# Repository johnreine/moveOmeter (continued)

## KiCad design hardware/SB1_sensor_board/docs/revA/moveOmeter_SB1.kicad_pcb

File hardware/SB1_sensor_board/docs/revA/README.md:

# moveOmeter sensor board SB1 (rev A draft, placed, not routed)

One HLK-LD6004 (60 GHz) and one HLK-LD2450 (24 GHz) on a 70 x 56.5 mm board with TB1's mounting holes. Each sensor
has its own USB-C port and USB-serial chip, so a PC can run both sensors with no mainboard. A 20-pin ribbon carries
5 V in and both serial ports out to the mainboard. Generated 2026-10-25 from `tools/` (same generator as TB1); on
2026-10-26 the ribbon header was stood on end and cut from 26 to 20 pins, and the board re-placed.

**Product arrangement:** two identical SB1s per frame or nightlight, fronts 90 degrees apart in a V with the point toward
the room (`docs/SB1_arrangement.png`).
- **Coverage:** each board points 45 degrees off straight-out, so every direction in front of the wall is within 45
  degrees of one radar's axis. With +/-60 degree radars that leaves 15 degrees to spare at the edges, about 210 degrees
  per radar type, and about 30 degrees of overlap straight ahead. A third board isn't needed.
- **Mainboard:** directly behind the two SB1s. It takes both ribbons on two 2x10 headers that also stand on end, at the
  same height as J3. Each flat cable then runs level, edge-on, and only bends sideways (the easy way) through the 45
  degrees between the boards.

## Open it

Open `moveOmeter_SB1.kicad_pro` in KiCad 10. The schematics are KiCad 8 format until KiCad saves them. Project
libraries: `lib/SB1.kicad_sym` and `lib/SB1.pretty` (radar modules and the front-mount hole, copied from TB1). Run ERC,
then Update PCB from Schematic (F8): it should only refresh fields. Run DRC before routing.

## Sheets

| Sheet | File | Contents |
| --- | --- | --- |
| Power_USB | power_usb.kicad_sch | 2x USB-C + USBLC6 + CH340C, 2x TPS2113A 5 V mux, BAT54C + LP5907 3.3 V logic rail, 20-pin ribbon, INA219 address jumper |
| LD6004 | ld6004.kicad_sch | TLV62569 3.3 V buck, INA219, rail discharge, TX gate, ESD, board-mounted module |
| LD2450 | ld2450.kicad_sch | TPS2051C 5 V switch, INA219, rail discharge, TX gate, ESD, board-mounted module |

## How it works

- **Power:** each sensor's 5 V comes from a TPS2113A that prefers the ribbon's 5 V and falls back to that sensor's
  USB-C. Neither input can back-feed the other (the mux FETs have no body diodes). USB-C A powers the LD6004 and USB-C
  B the LD2450, so each sensor gets a whole USB port. The 3.3 V logic rail (CH340Cs, monitors, gates) comes from
  either sensor's 5 V through a BAT54C and an LP5907 LDO.
- **Serial:** the sensor's TX goes to both its CH340C and the ribbon through 1k each. A 3-input AND gate
  (SN74LVC1G11) drives the sensor's RX from the CH340C TX, the ribbon TX and a "sensor rail is up" sense, so either
  host can talk (an idle UART line is high). The gate's output is held low while the sensor is off, so nothing
  back-powers it.
- **On/off:** each sensor is on by default (100k pull-up on EN).
  - The mainboard turns it off by pulling its ribbon EN line low.
  - The PC turns it off by asserting DTR with RTS released (a 2N7002 from RTS# to DTR#). Opening the port asserts both
    lines, which leaves the sensor on. In pyserial: `ser.rts = False; ser.dtr = True` for off, `ser.dtr = False` for
    on.
  - When EN goes low, the rail-discharge FET pulls the sensor rail to 0 V, so a power cycle is a clean reset.
- **Status lines:** LD6004 P20 and the LD2450 switch fault flag go to the ribbon and to each CH340C's CTS# input.
- **Current monitors:** INA219s at 0x40 (LD6004) and 0x44 (LD2450). Bridge solder jumper ADDR B on the second board
  of a pair to move them to 0x41 / 0x45. The I2C pull-ups are on the mainboard.

## Ribbon (J3, 2x10 shrouded header, 2.54 mm)

Wire n on the flat cable is pin n, and the cable is straight through, so the mainboard's headers use the same
pinout. The two +5 V wires and every serial and I2C wire have a ground wire on each side. The four enable / status
lines barely change, so they're grouped at the end without grounds between them.

| Pin | Signal | Pin | Signal |
| --- | --- | --- | --- |
| 1 | GND | 2 | +5 V in |
| 3 | +5 V in | 4 | GND |
| 5 | LD6004 TX (mainboard to sensor) | 6 | GND |
| 7 | LD6004 RX (sensor to mainboard) | 8 | GND |
| 9 | LD2450 TX (mainboard to sensor) | 10 | GND |
| 11 | LD2450 RX (sensor to mainboard) | 12 | GND |
| 13 | I2C SDA | 14 | GND |
| 15 | I2C SCL | 16 | GND |
| 17 | LD6004 enable (low = off) | 18 | LD2450 enable (low = off) |
| 19 | LD6004 P20 | 20 | LD2450 fault (low = fault) |

Seen from behind, pin 1 is at the top, odd pins in the left column, and the shroud's key slot on the left.

UART logic is 3.3 V. Baud rates: LD6004 115200, LD2450 256000. The CH340C makes 256000 as 12 MHz / 47 = 255.3 kbaud
(-0.3 %).

## Layout (70 x 56.5 mm, placed 2026-10-26, not routed)

- **Holes:** TB1's four M3 holes and footprint, with 0.27 in front-mount clearance. J3's shroud sets the board height:
  56.5 mm, 1.5 mm taller than the 70 x 55 mm v0.1 board whose holes it shares (64 mm with the 2x13 header).
- **Front:** LD6004 on the top edge, LD2450 under it (same positions as TB1), and the radar circuitry below them.
- **Back:** the ribbon header J3, a straight shrouded 2x10 standing on end (long side top to bottom), centred
  left-right. Its pins run from just below the LD2450 (27.6 mm from the top edge, pin 1 at the top) to 50.5 mm, and the
  shroud ends about 1 mm from the bottom edge. The cable leaves straight back, edge-on, toward the mainboard.
  - It can't sit behind the radars: no through-hole pins there, so the ground stays solid.
  - It can't sit near a side edge: on one board of each pair that edge is the point of the V, and the plug would hit
    the other board.
  - Also on the back: both USB-C ports on the bottom edge at the corners (bench use; unused in the unit), the
    USB-serial chips, the 5 V muxes and the 3.3 V LDO.
- Nothing is on the side edges: with two identical boards in a V, one board's outer edge is the other's inner edge.
- **Stackup:** 4 layers, F.Cu signals + GND / In1 GND / In2 +3V3 / B.Cu signals + GND. Fill zones after routing.
- **Checks:** all rule checks pass (mount clearance, radar fields of view, no through-hole pins behind the radars,
  edges, nets).

## Ordering

`bom_board.csv` has DigiKey numbers and qty-1 prices: about $49 a board, not counting the two radar modules. The
exception is the CH340C: WCH chips aren't sold by DigiKey or Mouser, so it comes from LCSC (part C84681). Buy a few
spares.

The ribbon cable isn't in the BOM, because its length depends on the mainboard. Any keyed 20-way 2.54 mm IDC cable
with a socket on each end fits. One example is Assmann H3AAH-2006G (LCSC C1770517), which can go in the same order as
the CH340Cs.

## Ready for rev B: mic socket

Rev B (decided on the 10/26 evening drive, not built yet) gets two Adafruit I2S mic breakouts per board. Their socket
is already in the libraries: symbol `SB1:I2S_Mic_Breakout`, footprint `SB1:Adafruit_I2S_Mic_Breakout_Socket_1x06`.

- **Breakouts:** Adafruit 6049 (TDK ICS-43434) or 3421 (Knowles SPH0645). Adafruit's board files show the same
  16.51 x 12.7 mm outline, header, sound-hole position and holes, so either plugs in. Adafruit's 6049 page says the
  ICS-43434 is discontinued and names the SPH0645 as its replacement.
- **Amazon clone (B0FMDGRM8F, silk "MRS179A"), 10/26:** a copy of Adafruit's 6049 layout. From the listing photo: same
  pin order (3V, GND, BCLK, DOUT, LRCL, SEL), same parts, sound hole about 5.3-5.5 mm from the pin row and centred,
  holes about 11.4 mm apart. The board may be up to ~1 mm narrower on the header side, which stays inside the
  footprint's outline. The listing calls SEL an I2S / PDM select; on the ICS-43434 it's the left / right channel
  select, as on Adafruit's board (the chip is I2S only). Fits the same socket.
- **Pins (from Adafruit's board files):** 1 3V, 2 GND, 3 BCLK, 4 DOUT, 5 LRCL (WS), 6 SEL. SEL low = left channel,
  high = right, so the two mics on a board share one data line.
- **Mounting:** a 1x6 female socket (Sullins PPTC061LFBN-RC, 8.5 mm) on SB1's front. Solder the breakout's header
  with its plastic on the chip side (the side shown in Adafruit's photo), so the pins point away from that side and
  the sound hole faces the room. The breakout lies parallel to SB1, its sound hole about 12.6 mm off the board.
  Seen from the front, pin 1 (3V) is at the right, on the square pad.
- **Check print:** `docs/SB1_mic_socket_1to1.pdf` (print at 100 %, check the 50 mm bar). Lay a breakout on it sound
  hole up: the pins should land on the pads with 3V on the square pad, and the sound hole on the cross.
- **Source:** `tools/layout/mkmicfp.py` writes the footprint; `tools/layout/render_micfp.py` draws the check print.

## Regenerating

- `python3 tools/build.py <out>` writes the schematics, symbol library, netlist report and BOM. Parts and nets are in
  `tools/design.py`, ordering data in `tools/vendor.py`.
- `tools/layout/` writes and checks the board (see its README): `plan_sb1.py`, `place_sb1.py`, `mkpcb_sb1.py`,
  `verify_sb1.py`. `render2.py` draws it (`docs/SB1_board.png`). `arrangement.py` draws the three-board sketch.
- Once you edit in KiCad, KiCad is the source of truth.

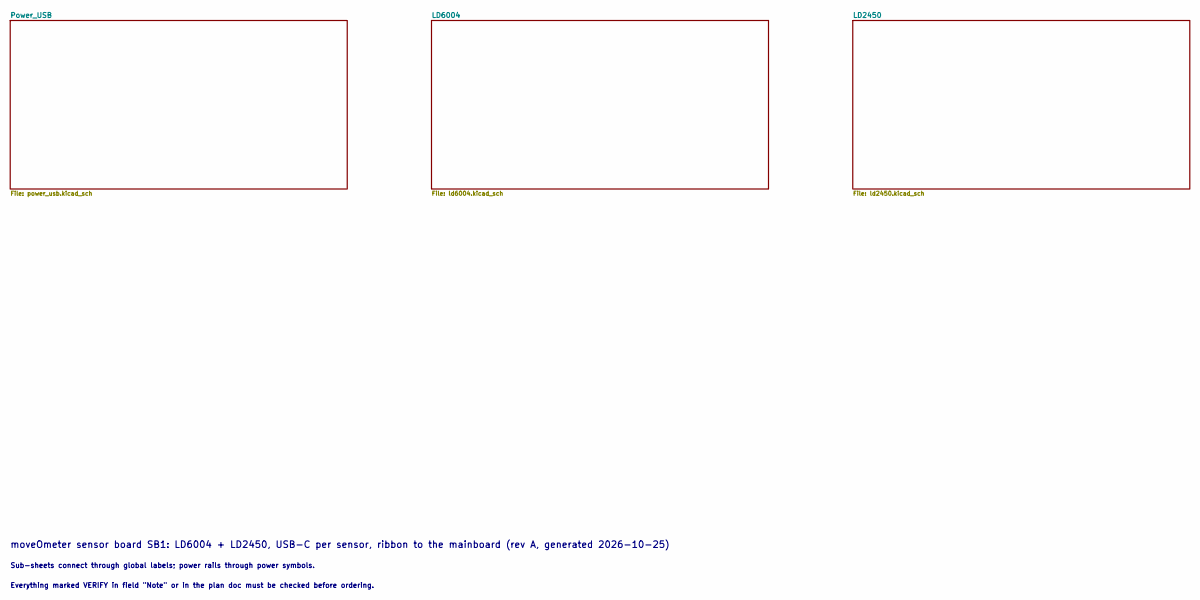
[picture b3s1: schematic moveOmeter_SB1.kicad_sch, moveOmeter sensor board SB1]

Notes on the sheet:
moveOmeter sensor board SB1: LD6004 + LD2450, USB-C per sensor, ribbon to the mainboard (rev A, generated 2026-10-25)
Sub-sheets connect through global labels; power rails through power symbols.
Everything marked VERIFY in field "Note" or in the plan doc must be checked before ordering.

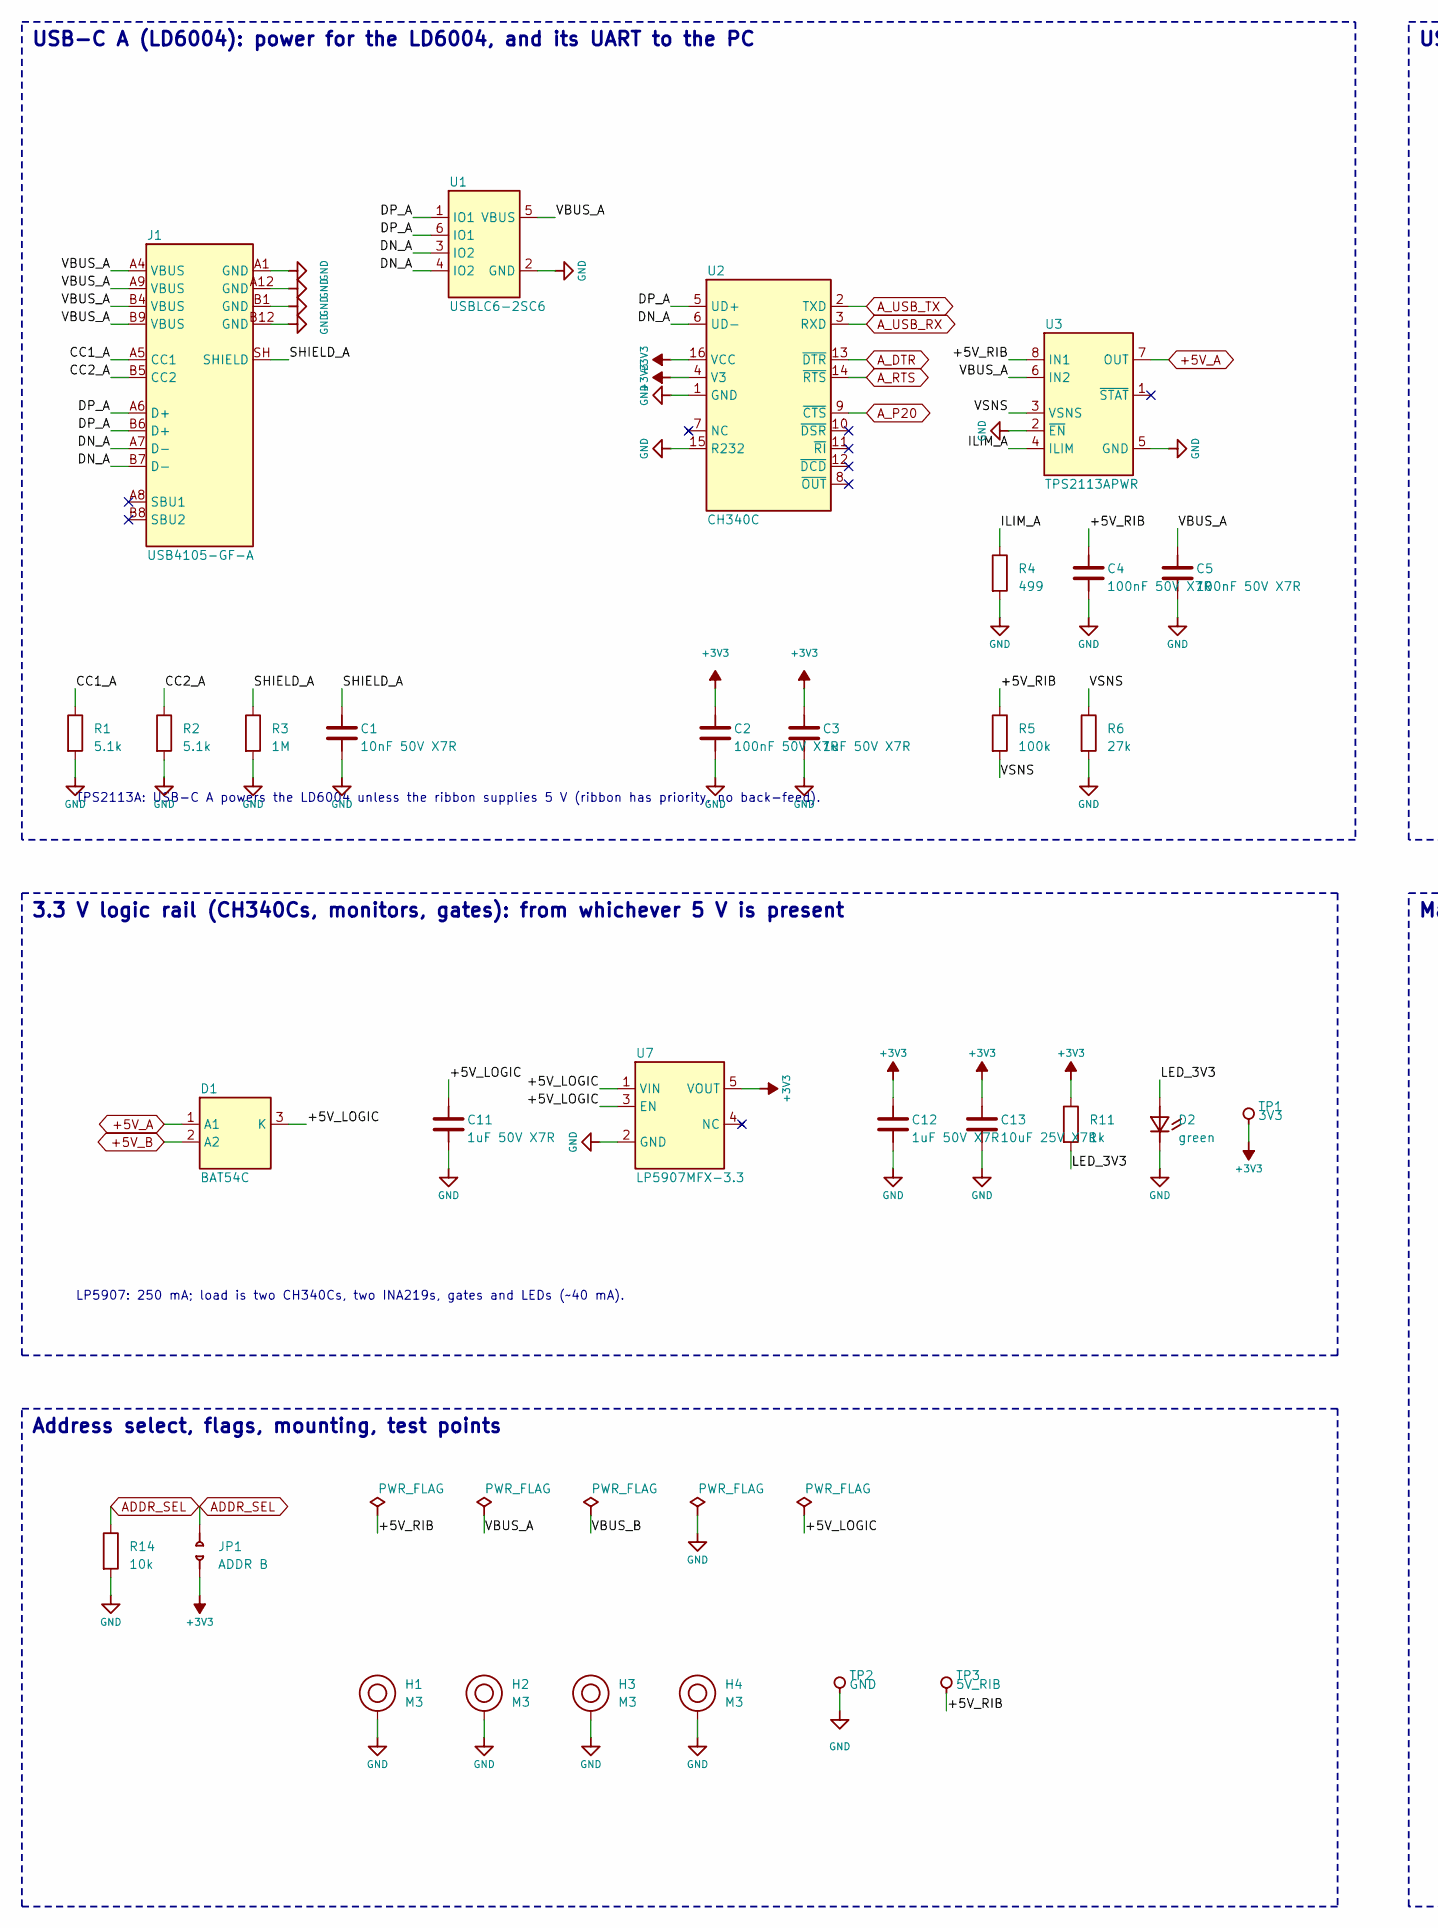
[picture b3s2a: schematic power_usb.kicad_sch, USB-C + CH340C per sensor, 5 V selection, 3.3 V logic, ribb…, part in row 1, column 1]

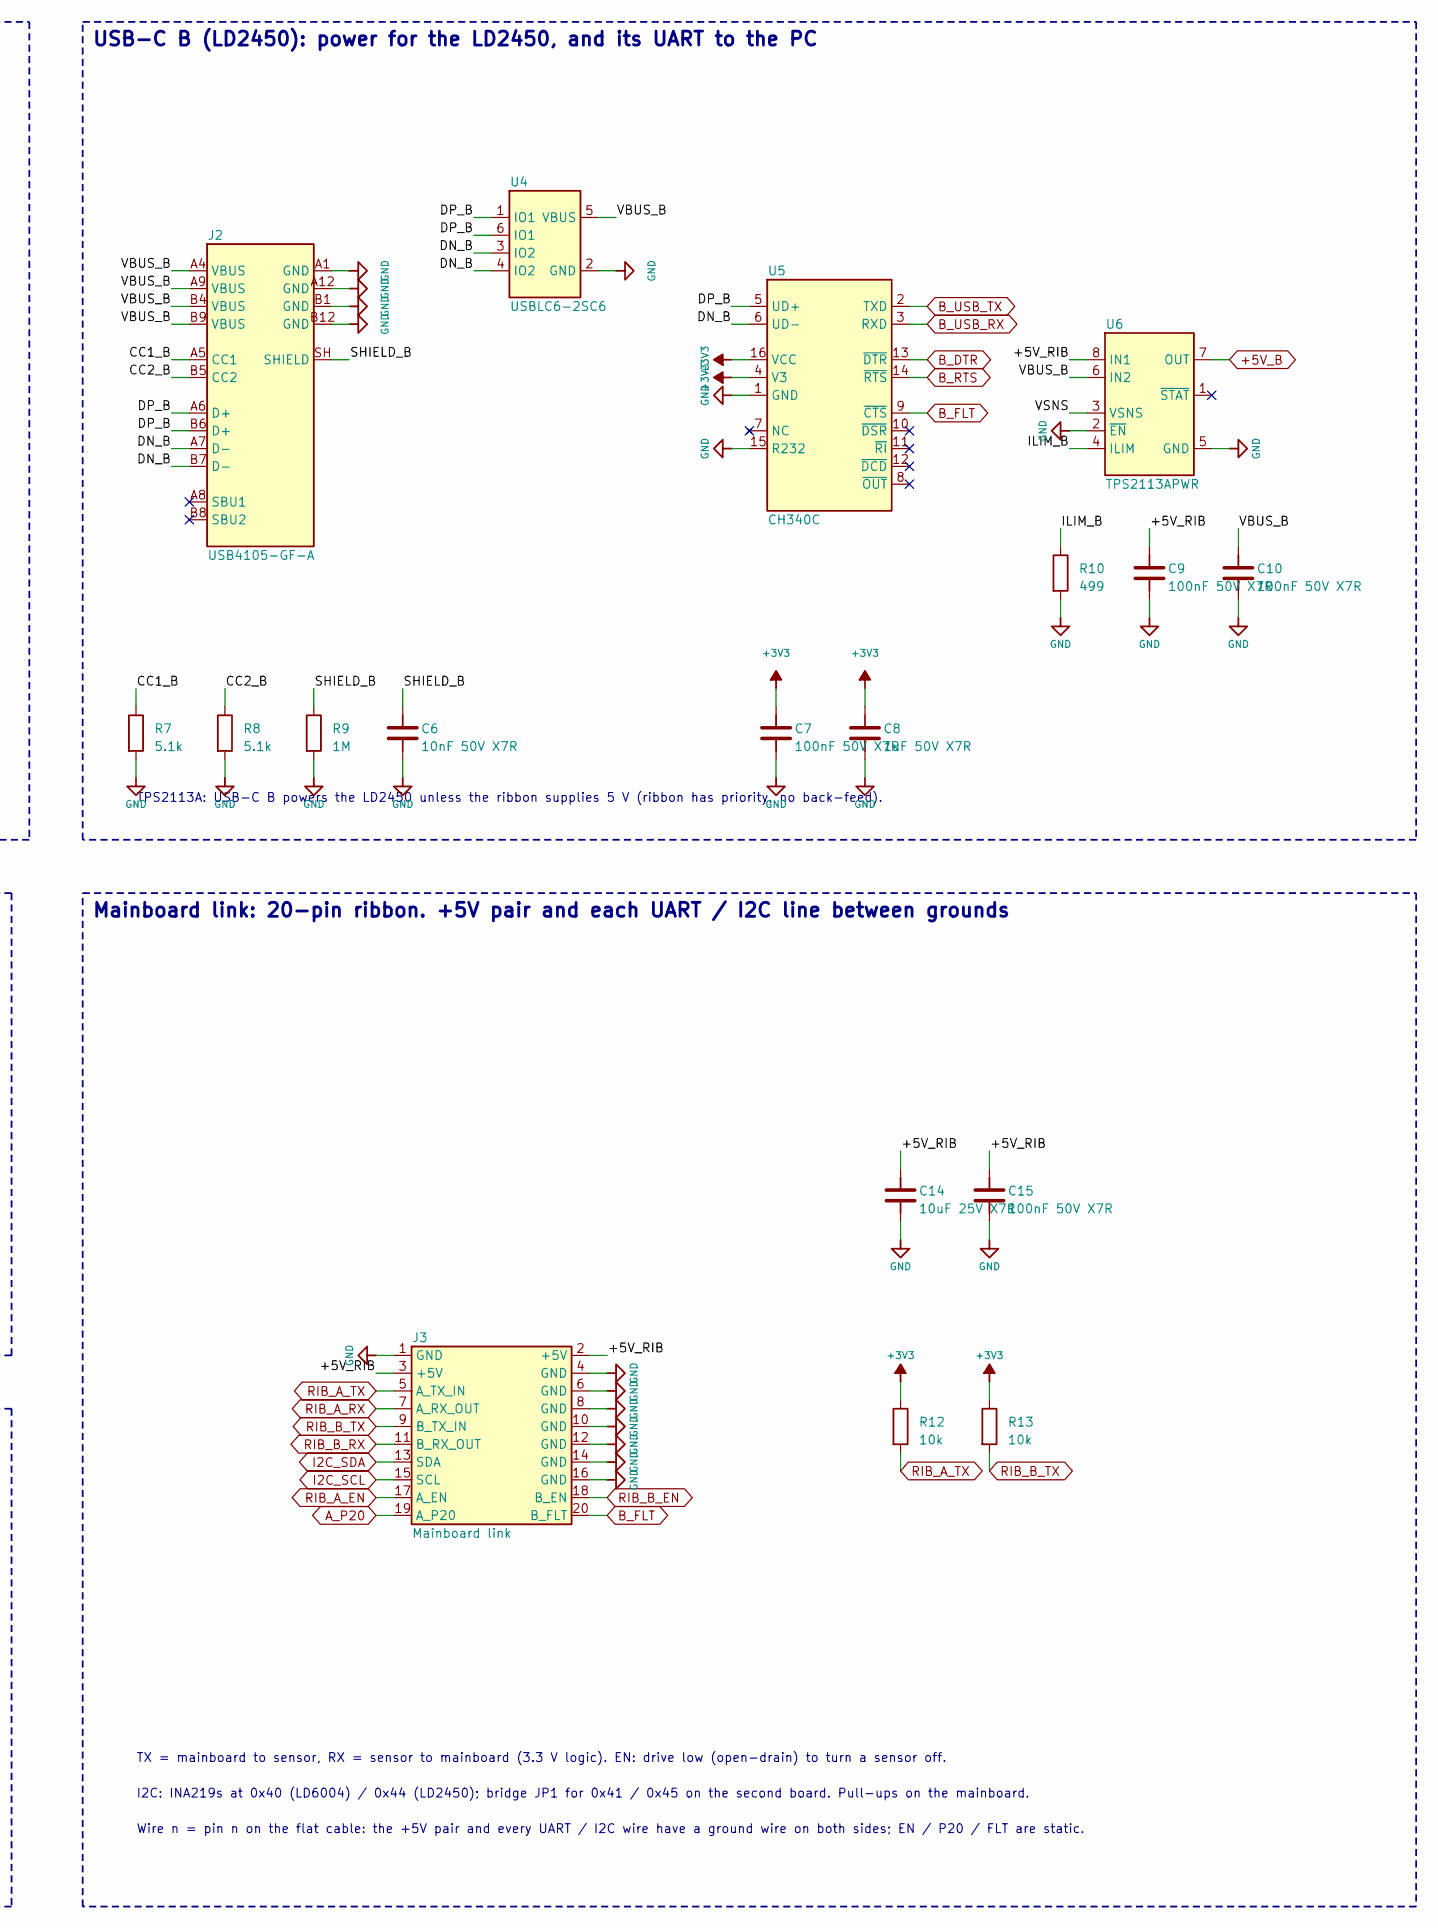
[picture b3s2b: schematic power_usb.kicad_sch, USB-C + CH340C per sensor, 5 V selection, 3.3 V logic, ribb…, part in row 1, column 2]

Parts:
C1, C6: 10nF 50V X7R; C_1206_3216Metric_Pad1.33x1.80mm_HandSolder; MPN C1206C103K5RACTU
C2, C4, C5, C7, C9, C10, C15: 100nF 50V X7R; C_1206_3216Metric_Pad1.33x1.80mm_HandSolder; MPN CL31B104KBCNNNC
C3, C8, C11, C12: 1uF 50V X7R; C_1206_3216Metric_Pad1.33x1.80mm_HandSolder; MPN CC1206KKX7R9BB105
C13, C14: 10uF 25V X7R; C_1210_3225Metric_Pad1.33x2.70mm_HandSolder; MPN GRM32DR71E106KA12L
D1: BAT54C; SOT-23; MPN BAT54CLT1G
D2: green; LED_1206_3216Metric_Pad1.42x1.75mm_HandSolder; MPN LTST-C150GKT
H1, H2, H3, H4: M3; MountingHole_3.2mm_M3_DIN965_Pad_TopOnly_FrontMount
J1, J2: USB4105-GF-A; USB_C_Receptacle_GCT_USB4105-xx-A_16P_TopMnt_Horizontal; MPN USB4105-GF-A
J3: Mainboard link; IDC-Header_2x10_P2.54mm_Vertical; MPN SBH11-PBPC-D10-ST-BK
JP1: ADDR B; SolderJumper-2_P1.3mm_Open_RoundedPad1.0x1.5mm
R1, R2, R7, R8: 5.1k; R_1206_3216Metric_Pad1.30x1.75mm_HandSolder; MPN RC1206FR-075K1L
R3, R9: 1M; R_1206_3216Metric_Pad1.30x1.75mm_HandSolder; MPN RC1206FR-071ML
R4, R10: 499; R_1206_3216Metric_Pad1.30x1.75mm_HandSolder; MPN RC1206FR-07499RL
R5: 100k; R_1206_3216Metric_Pad1.30x1.75mm_HandSolder; MPN RC1206FR-07100KL
R6: 27k; R_1206_3216Metric_Pad1.30x1.75mm_HandSolder; MPN RC1206FR-0727KL
R11: 1k; R_1206_3216Metric_Pad1.30x1.75mm_HandSolder; MPN RC1206FR-071KL
R12, R13, R14: 10k; R_1206_3216Metric_Pad1.30x1.75mm_HandSolder; MPN RC1206FR-0710KL
TP1: 3V3; TestPoint_Keystone_5000-5004_Miniature; MPN 5000
TP2: GND; TestPoint_Keystone_5000-5004_Miniature; MPN 5001
TP3: 5V_RIB; TestPoint_Keystone_5000-5004_Miniature; MPN 5000
U1, U4: USBLC6-2SC6; SOT-23-6; MPN USBLC6-2SC6
U2, U5: CH340C; SOIC-16_3.9x9.9mm_P1.27mm; MPN CH340C
U3, U6: TPS2113APWR; TSSOP-8_4.4x3mm_P0.65mm; MPN TPS2113APWR
U7: LP5907MFX-3.3; SOT-23-5; MPN LP5907MFX-3.3/NOPB

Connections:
+3V3: C2.1, C3.1, C7.1, C8.1, C12.1, C13.1, JP1.2, R11.1, R12.1, R13.1, TP1.1, U2.4 (V3), U2.16 (VCC), U5.4 (V3), U5.16 (VCC), U7.5 (VOUT); also elsewhere on the board
+5V_A: D1.1 (A1), U3.7 (OUT); also elsewhere on the board
+5V_B: D1.2 (A2), U6.7 (OUT); also elsewhere on the board
/Power_USB/+5V_LOGIC: C11.1, D1.3 (K), U7.1 (VIN), U7.3 (EN)
/Power_USB/+5V_RIB: C4.1, C9.1, C14.1, C15.1, J3.2 (+5V), J3.3 (+5V), R5.1, TP3.1, U3.8 (IN1), U6.8 (IN1)
/Power_USB/CC1_A: J1.A5 (CC1), R1.1
/Power_USB/CC1_B: J2.A5 (CC1), R7.1
/Power_USB/CC2_A: J1.B5 (CC2), R2.1
/Power_USB/CC2_B: J2.B5 (CC2), R8.1
/Power_USB/DN_A: J1.A7 (D-), J1.B7 (D-), U1.3 (IO2), U1.4 (IO2), U2.6 (UD-)
/Power_USB/DN_B: J2.A7 (D-), J2.B7 (D-), U4.3 (IO2), U4.4 (IO2), U5.6 (UD-)
/Power_USB/DP_A: J1.A6 (D+), J1.B6 (D+), U1.1 (IO1), U1.6 (IO1), U2.5 (UD+)
/Power_USB/DP_B: J2.A6 (D+), J2.B6 (D+), U4.1 (IO1), U4.6 (IO1), U5.5 (UD+)
/Power_USB/ILIM_A: R4.1, U3.4 (ILIM)
/Power_USB/ILIM_B: R10.1, U6.4 (ILIM)
/Power_USB/LED_3V3: D2.2 (A), R11.2
/Power_USB/SHIELD_A: C1.1, J1.SH (SHIELD), R3.1
/Power_USB/SHIELD_B: C6.1, J2.SH (SHIELD), R9.1
/Power_USB/VBUS_A: C5.1, J1.A4 (VBUS), J1.A9 (VBUS), J1.B4 (VBUS), J1.B9 (VBUS), U1.5 (VBUS), U3.6 (IN2)
/Power_USB/VBUS_B: C10.1, J2.A4 (VBUS), J2.A9 (VBUS), J2.B4 (VBUS), J2.B9 (VBUS), U4.5 (VBUS), U6.6 (IN2)
/Power_USB/VSNS: R5.2, R6.1, U3.3 (VSNS), U6.3 (VSNS)
ADDR_SEL: JP1.1, R14.1; also elsewhere on the board
A_DTR: U2.13 (~DTR); also elsewhere on the board
A_P20: J3.19 (A_P20), U2.9 (~CTS); also elsewhere on the board
A_RTS: U2.14 (~RTS); also elsewhere on the board
A_USB_RX: U2.3 (RXD); also elsewhere on the board
A_USB_TX: U2.2 (TXD); also elsewhere on the board
B_DTR: U5.13 (~DTR); also elsewhere on the board
B_FLT: J3.20 (B_FLT), U5.9 (~CTS); also elsewhere on the board
B_RTS: U5.14 (~RTS); also elsewhere on the board
B_USB_RX: U5.3 (RXD); also elsewhere on the board
B_USB_TX: U5.2 (TXD); also elsewhere on the board
GND: C1.2, C2.2, C3.2, C4.2, C5.2, C6.2, C7.2, C8.2, C9.2, C10.2, C11.2, C12.2, C13.2, C14.2, C15.2, D2.1 (K), H1.1, H2.1, H3.1, H4.1, J1.A1 (GND), J1.A12 (GND), J1.B1 (GND), J1.B12 (GND), J2.A1 (GND), J2.A12 (GND), J2.B1 (GND), J2.B12 (GND), J3.1 (GND), J3.4 (GND), J3.6 (GND), J3.8 (GND), J3.10 (GND), J3.12 (GND), J3.14 (GND), J3.16 (GND), R1.2, R2.2, R3.2, R4.2, R6.2, R7.2, R8.2, R9.2, R10.2, R14.2, TP2.1, U1.2 (GND), U2.1 (GND), U2.15 (R232), U3.2 (~EN), U3.5 (GND), U4.2 (GND), U5.1 (GND), U5.15 (R232), U6.2 (~EN), U6.5 (GND), U7.2 (GND); also elsewhere on the board
I2C_SCL: J3.15 (SCL); also elsewhere on the board
I2C_SDA: J3.13 (SDA); also elsewhere on the board
RIB_A_EN: J3.17 (A_EN); also elsewhere on the board
RIB_A_RX: J3.7 (A_RX_OUT); also elsewhere on the board
RIB_A_TX: J3.5 (A_TX_IN), R12.2; also elsewhere on the board
RIB_B_EN: J3.18 (B_EN); also elsewhere on the board
RIB_B_RX: J3.11 (B_RX_OUT); also elsewhere on the board
RIB_B_TX: J3.9 (B_TX_IN), R13.2; also elsewhere on the board

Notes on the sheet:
USB-C A (LD6004): power for the LD6004, and its UART to the PC
TPS2113A: USB-C A powers the LD6004 unless the ribbon supplies 5 V (ribbon has priority, no back-feed).
USB-C B (LD2450): power for the LD2450, and its UART to the PC
TPS2113A: USB-C B powers the LD2450 unless the ribbon supplies 5 V (ribbon has priority, no back-feed).
3.3 V logic rail (CH340Cs, monitors, gates): from whichever 5 V is present
LP5907: 250 mA; load is two CH340Cs, two INA219s, gates and LEDs (~40 mA).
Mainboard link: 20-pin ribbon. +5V pair and each UART / I2C line between grounds
TX = mainboard to sensor, RX = sensor to mainboard (3.3 V logic). EN: drive low (open-drain) to turn a sensor off.
I2C: INA219s at 0x40 (LD6004) / 0x44 (LD2450); bridge JP1 for 0x41 / 0x45 on the second board. Pull-ups on the mainboard.
Wire n = pin n on the flat cable: the +5V pair and every UART / I2C wire have a ground wire on both sides; EN / P20 / FLT are static.
Address select, flags, mounting, test points

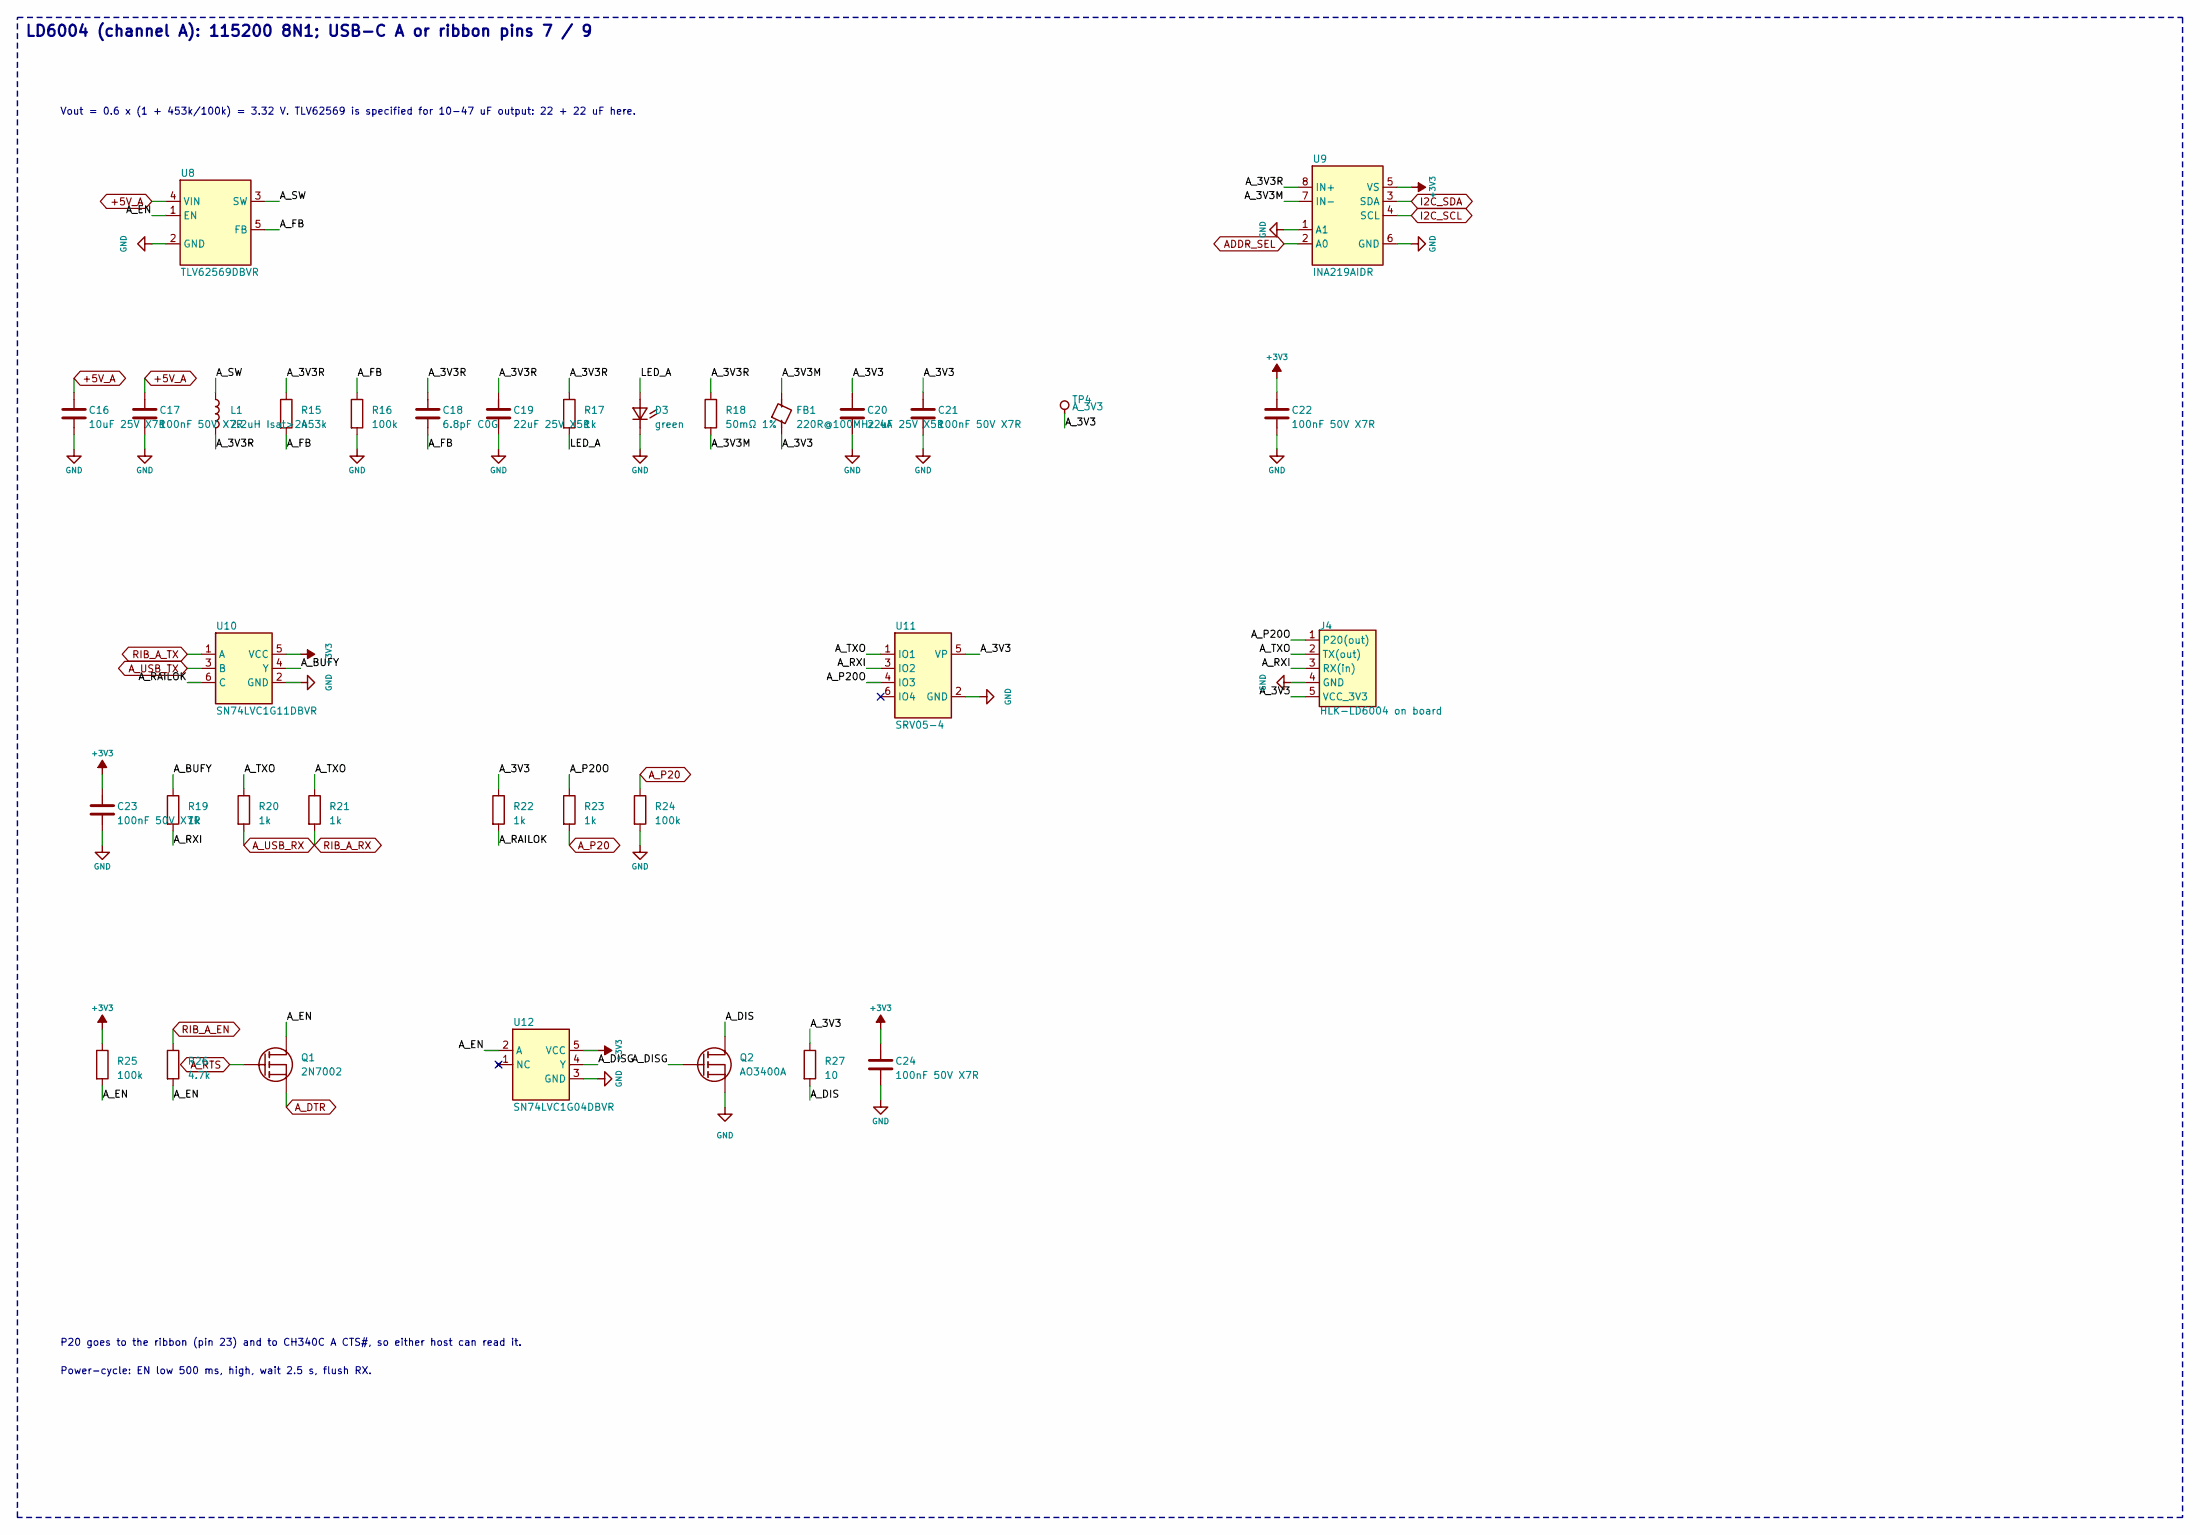
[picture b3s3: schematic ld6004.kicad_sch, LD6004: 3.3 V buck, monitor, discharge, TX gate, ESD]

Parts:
C16: 10uF 25V X7R; C_1210_3225Metric_Pad1.33x2.70mm_HandSolder; MPN GRM32DR71E106KA12L
C17, C21, C22, C23, C24: 100nF 50V X7R; C_1206_3216Metric_Pad1.33x1.80mm_HandSolder; MPN CL31B104KBCNNNC
C18: 6.8pF C0G; C_1206_3216Metric_Pad1.33x1.80mm_HandSolder; MPN CC1206CRNPO9BN6R8
C19, C20: 22uF 25V X5R; C_1210_3225Metric_Pad1.33x2.70mm_HandSolder; MPN GRM32ER61E226KE15L
D3: green; LED_1206_3216Metric_Pad1.42x1.75mm_HandSolder; MPN LTST-C150GKT
FB1: 220R@100MHz 4A; L_1206_3216Metric_Pad1.22x1.90mm_HandSolder; MPN LSMGA321616T221NG
J4: HLK-LD6004 on board; HLK-LD6004_Module_2x1x05_P1.27mm; MPN LPPB051NFFN-RC
L1: 2.2uH Isat>2A; L_Bourns-SRN4018; MPN SRN4018-2R2M
Q1: 2N7002; SOT-23; MPN 2N7002LT1G
Q2: AO3400A; SOT-23; MPN AO3400A
R15: 453k; R_1206_3216Metric_Pad1.30x1.75mm_HandSolder; MPN RC1206FR-07453KL
R16, R24, R25: 100k; R_1206_3216Metric_Pad1.30x1.75mm_HandSolder; MPN RC1206FR-07100KL
R17, R19, R20, R21, R22, R23: 1k; R_1206_3216Metric_Pad1.30x1.75mm_HandSolder; MPN RC1206FR-071KL
R18: 50mΩ 1%; R_1206_3216Metric_Pad1.30x1.75mm_HandSolder; MPN WSL1206R0500FEA
R26: 4.7k; R_1206_3216Metric_Pad1.30x1.75mm_HandSolder; MPN RC1206FR-074K7L
R27: 10; R_1206_3216Metric_Pad1.30x1.75mm_HandSolder; MPN RC1206FR-0710RL
TP4: A_3V3; TestPoint_Keystone_5000-5004_Miniature; MPN 5000
U8: TLV62569DBVR; SOT-23-5; MPN TLV62569DBVR
U9: INA219AIDR; SOIC-8_3.9x4.9mm_P1.27mm; MPN INA219AIDR
U10: SN74LVC1G11DBVR; SOT-23-6; MPN SN74LVC1G11DBVR
U11: SRV05-4; SOT-23-6; MPN SRV05-4.TCT
U12: SN74LVC1G04DBVR; SOT-23-5; MPN SN74LVC1G04DBVR

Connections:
+3V3: C22.1, C23.1, C24.1, R25.1, U9.5 (VS), U10.5 (VCC), U12.5 (VCC); also elsewhere on the board
+5V_A: C16.1, C17.1, U8.4 (VIN); also elsewhere on the board
/LD6004/A_3V3: C20.1, C21.1, FB1.2, J4.5 (VCC_3V3), R22.1, R27.1, TP4.1, U11.5 (VP)
/LD6004/A_3V3M: FB1.1, R18.2, U9.7 (IN-)
/LD6004/A_3V3R: C18.1, C19.1, L1.2, R15.1, R17.1, R18.1, U9.8 (IN+)
/LD6004/A_BUFY: R19.1, U10.4 (Y)
/LD6004/A_DIS: Q2.3 (D), R27.2
/LD6004/A_DISG: Q2.1 (G), U12.4 (Y)
/LD6004/A_EN: Q1.3 (D), R25.2, R26.2, U8.1 (EN), U12.2 (A)
/LD6004/A_FB: C18.2, R15.2, R16.1, U8.5 (FB)
/LD6004/A_P20O: J4.1 (P20(out)), R23.1, U11.4 (IO3)
/LD6004/A_RAILOK: R22.2, U10.6 (C)
/LD6004/A_RXI: J4.3 (RX(in)), R19.2, U11.3 (IO2)
/LD6004/A_SW: L1.1, U8.3 (SW)
/LD6004/A_TXO: J4.2 (TX(out)), R20.1, R21.1, U11.1 (IO1)
/LD6004/LED_A: D3.2 (A), R17.2
ADDR_SEL: U9.2 (A0); also elsewhere on the board
A_DTR: Q1.2 (S); also elsewhere on the board
A_P20: R23.2, R24.1; also elsewhere on the board
A_RTS: Q1.1 (G); also elsewhere on the board
A_USB_RX: R20.2; also elsewhere on the board
A_USB_TX: U10.3 (B); also elsewhere on the board
GND: C16.2, C17.2, C19.2, C20.2, C21.2, C22.2, C23.2, C24.2, D3.1 (K), J4.4 (GND), Q2.2 (S), R16.2, R24.2, U8.2 (GND), U9.1 (A1), U9.6 (GND), U10.2 (GND), U11.2 (GND), U12.3 (GND); also elsewhere on the board
I2C_SCL: U9.4 (SCL); also elsewhere on the board
I2C_SDA: U9.3 (SDA); also elsewhere on the board
RIB_A_EN: R26.1; also elsewhere on the board
RIB_A_RX: R21.2; also elsewhere on the board
RIB_A_TX: U10.1 (A); also elsewhere on the board

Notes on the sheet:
LD6004 (channel A): 115200 8N1; USB-C A or ribbon pins 7 / 9
Vout = 0.6 x (1 + 453k/100k) = 3.32 V. TLV62569 is specified for 10-47 uF output: 22 + 22 uF here.
P20 goes to the ribbon (pin 23) and to CH340C A CTS#, so either host can read it.
Power-cycle: EN low 500 ms, high, wait 2.5 s, flush RX.

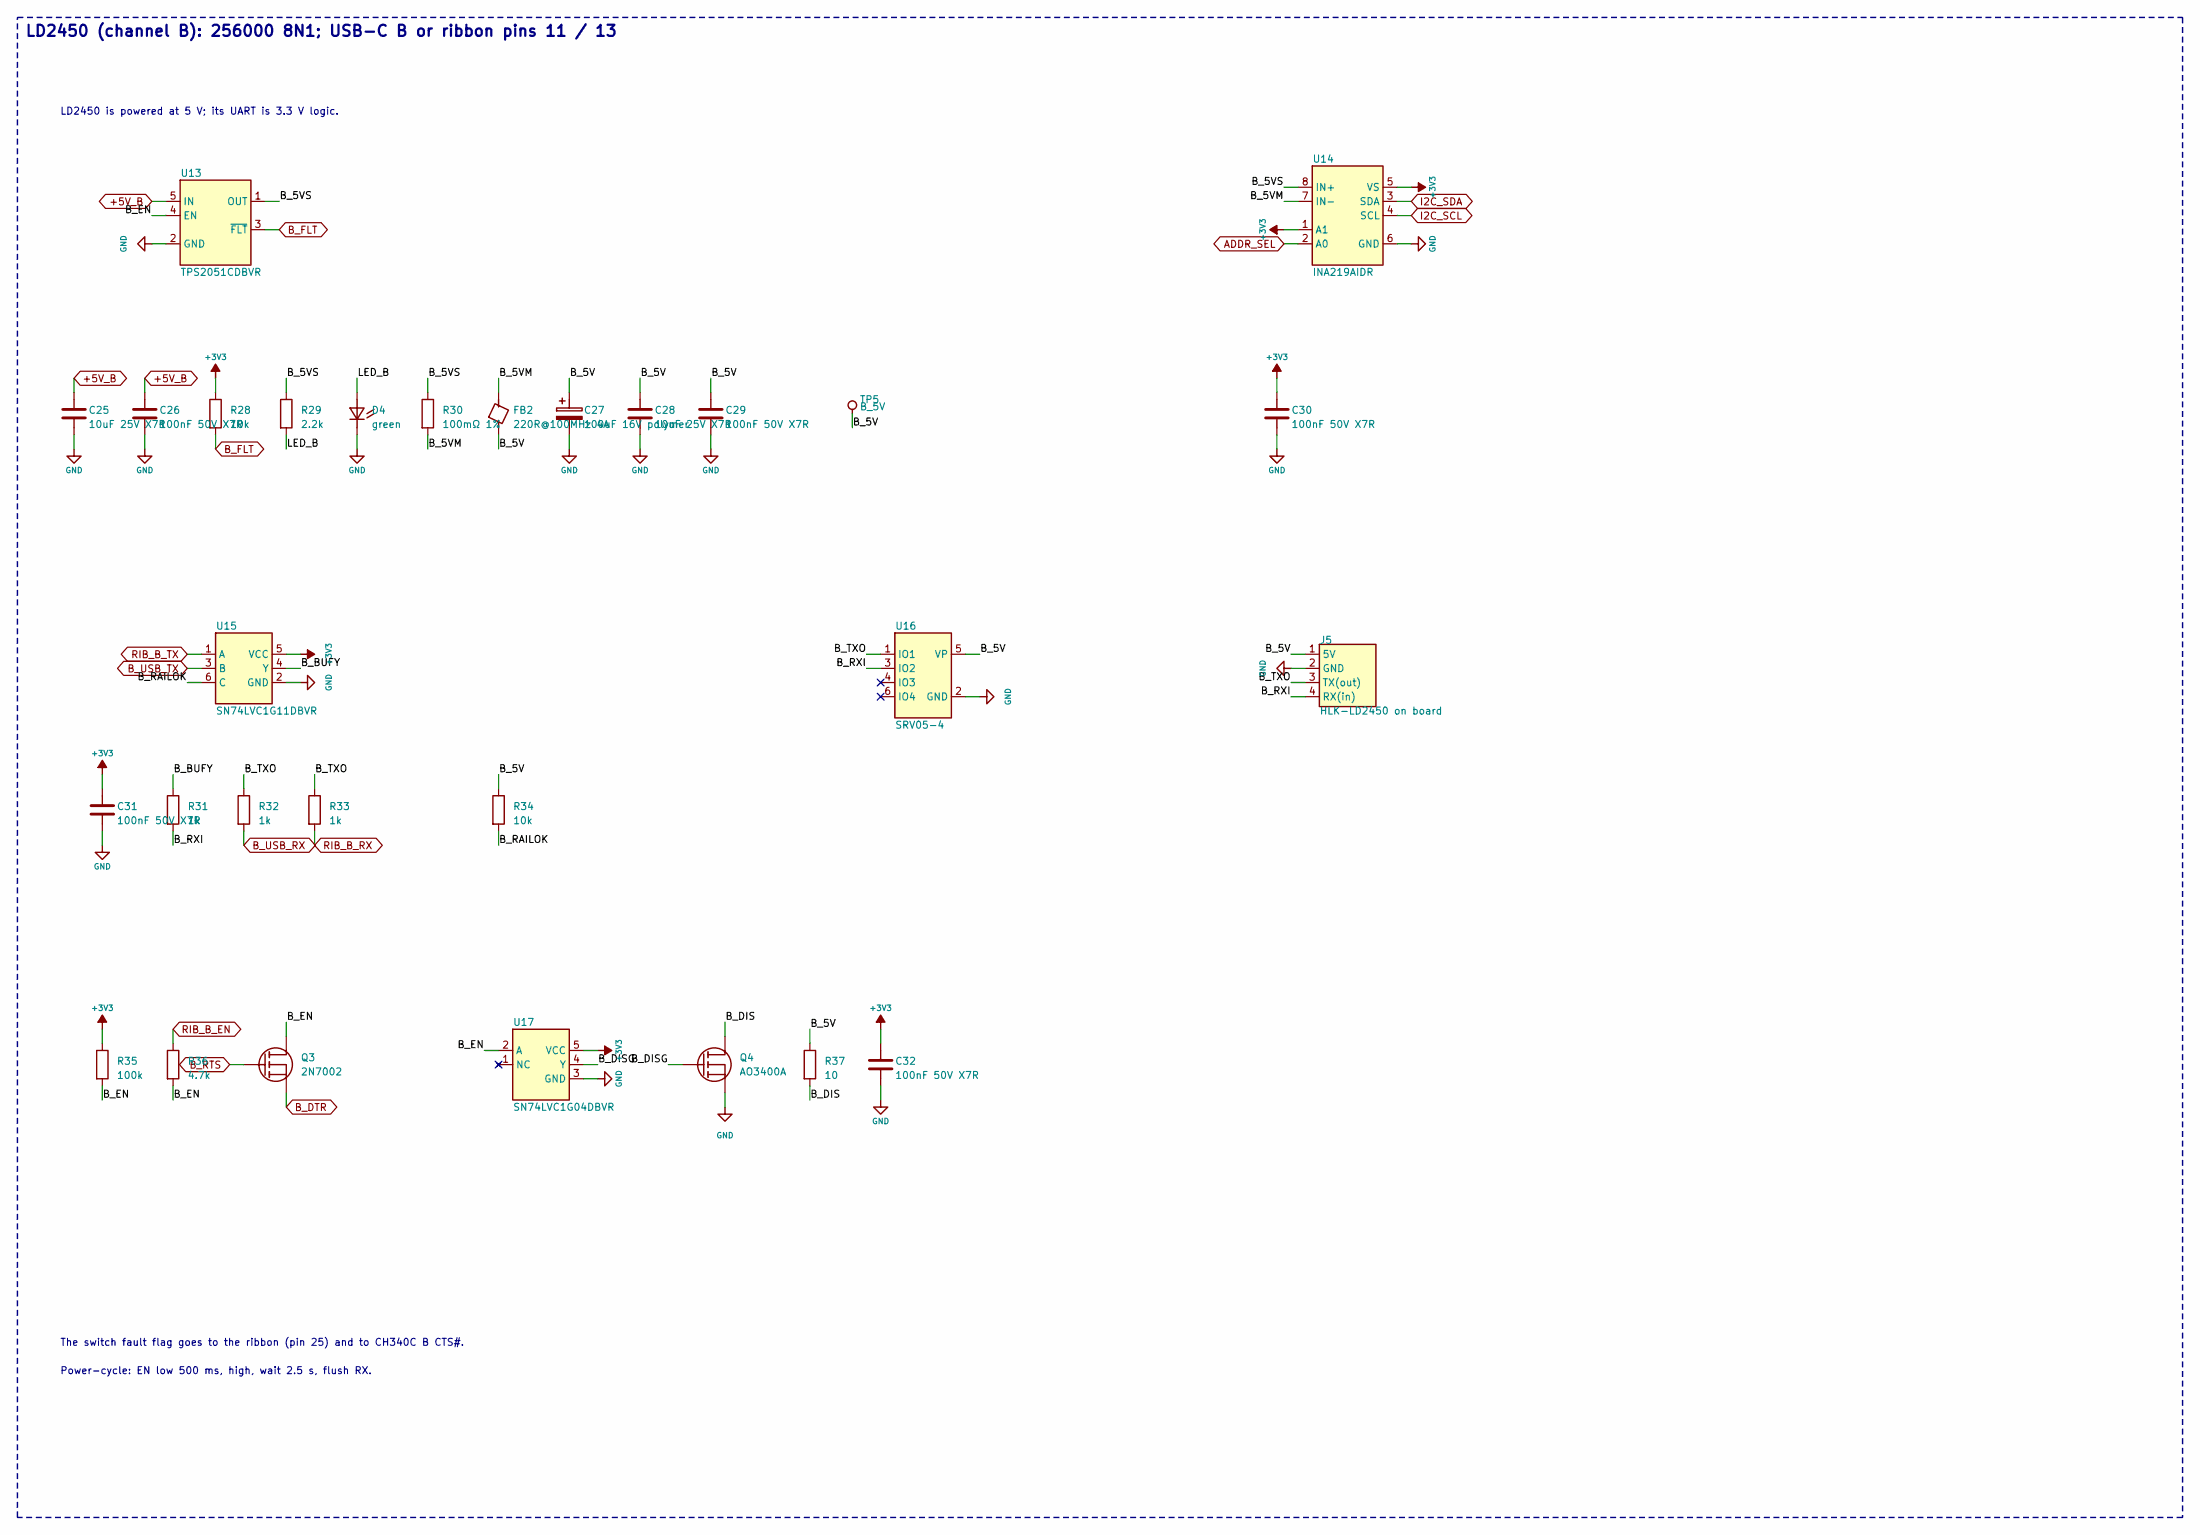
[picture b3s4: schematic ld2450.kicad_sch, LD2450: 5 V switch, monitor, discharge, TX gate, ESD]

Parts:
C25, C28: 10uF 25V X7R; C_1210_3225Metric_Pad1.33x2.70mm_HandSolder; MPN GRM32DR71E106KA12L
C26, C29, C30, C31, C32: 100nF 50V X7R; C_1206_3216Metric_Pad1.33x1.80mm_HandSolder; MPN CL31B104KBCNNNC
C27: 100uF 16V polymer; CP_Radial_D6.3mm_P2.50mm; MPN A759EK107M1CAAE018
D4: green; LED_1206_3216Metric_Pad1.42x1.75mm_HandSolder; MPN LTST-C150GKT
FB2: 220R@100MHz 4A; L_1206_3216Metric_Pad1.22x1.90mm_HandSolder; MPN LSMGA321616T221NG
J5: HLK-LD2450 on board; HLK-LD2450_Module_2x04_P2.00mm; MPN NPPN042AFCN-RC
Q3: 2N7002; SOT-23; MPN 2N7002LT1G
Q4: AO3400A; SOT-23; MPN AO3400A
R28, R34: 10k; R_1206_3216Metric_Pad1.30x1.75mm_HandSolder; MPN RC1206FR-0710KL
R29: 2.2k; R_1206_3216Metric_Pad1.30x1.75mm_HandSolder; MPN RC1206FR-072K2L
R30: 100mΩ 1%; R_1206_3216Metric_Pad1.30x1.75mm_HandSolder; MPN WSL1206R1000FEA
R31, R32, R33: 1k; R_1206_3216Metric_Pad1.30x1.75mm_HandSolder; MPN RC1206FR-071KL
R35: 100k; R_1206_3216Metric_Pad1.30x1.75mm_HandSolder; MPN RC1206FR-07100KL
R36: 4.7k; R_1206_3216Metric_Pad1.30x1.75mm_HandSolder; MPN RC1206FR-074K7L
R37: 10; R_1206_3216Metric_Pad1.30x1.75mm_HandSolder; MPN RC1206FR-0710RL
TP5: B_5V; TestPoint_Keystone_5000-5004_Miniature; MPN 5000
U13: TPS2051CDBVR; SOT-23-5; MPN TPS2051CDBVT
U14: INA219AIDR; SOIC-8_3.9x4.9mm_P1.27mm; MPN INA219AIDR
U15: SN74LVC1G11DBVR; SOT-23-6; MPN SN74LVC1G11DBVR
U16: SRV05-4; SOT-23-6; MPN SRV05-4.TCT
U17: SN74LVC1G04DBVR; SOT-23-5; MPN SN74LVC1G04DBVR

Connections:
+3V3: C30.1, C31.1, C32.1, R28.1, R35.1, U14.1 (A1), U14.5 (VS), U15.5 (VCC), U17.5 (VCC); also elsewhere on the board
+5V_B: C25.1, C26.1, U13.5 (IN); also elsewhere on the board
/LD2450/B_5V: C27.1 (+), C28.1, C29.1, FB2.2, J5.1 (5V), R34.1, R37.1, TP5.1, U16.5 (VP)
/LD2450/B_5VM: FB2.1, R30.2, U14.7 (IN-)
/LD2450/B_5VS: R29.1, R30.1, U13.1 (OUT), U14.8 (IN+)
/LD2450/B_BUFY: R31.1, U15.4 (Y)
/LD2450/B_DIS: Q4.3 (D), R37.2
/LD2450/B_DISG: Q4.1 (G), U17.4 (Y)
/LD2450/B_EN: Q3.3 (D), R35.2, R36.2, U13.4 (EN), U17.2 (A)
/LD2450/B_RAILOK: R34.2, U15.6 (C)
/LD2450/B_RXI: J5.4 (RX(in)), R31.2, U16.3 (IO2)
/LD2450/B_TXO: J5.3 (TX(out)), R32.1, R33.1, U16.1 (IO1)
/LD2450/LED_B: D4.2 (A), R29.2
ADDR_SEL: U14.2 (A0); also elsewhere on the board
B_DTR: Q3.2 (S); also elsewhere on the board
B_FLT: R28.2, U13.3 (~FLT); also elsewhere on the board
B_RTS: Q3.1 (G); also elsewhere on the board
B_USB_RX: R32.2; also elsewhere on the board
B_USB_TX: U15.3 (B); also elsewhere on the board
GND: C25.2, C26.2, C27.2 (-), C28.2, C29.2, C30.2, C31.2, C32.2, D4.1 (K), J5.2 (GND), Q4.2 (S), U13.2 (GND), U14.6 (GND), U15.2 (GND), U16.2 (GND), U17.3 (GND); also elsewhere on the board
I2C_SCL: U14.4 (SCL); also elsewhere on the board
I2C_SDA: U14.3 (SDA); also elsewhere on the board
RIB_B_EN: R36.1; also elsewhere on the board
RIB_B_RX: R33.2; also elsewhere on the board
RIB_B_TX: U15.1 (A); also elsewhere on the board

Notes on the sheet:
LD2450 (channel B): 256000 8N1; USB-C B or ribbon pins 11 / 13
LD2450 is powered at 5 V; its UART is 3.3 V logic.
The switch fault flag goes to the ribbon (pin 25) and to CH340C B CTS#.
Power-cycle: EN low 500 ms, high, wait 2.5 s, flush RX.
